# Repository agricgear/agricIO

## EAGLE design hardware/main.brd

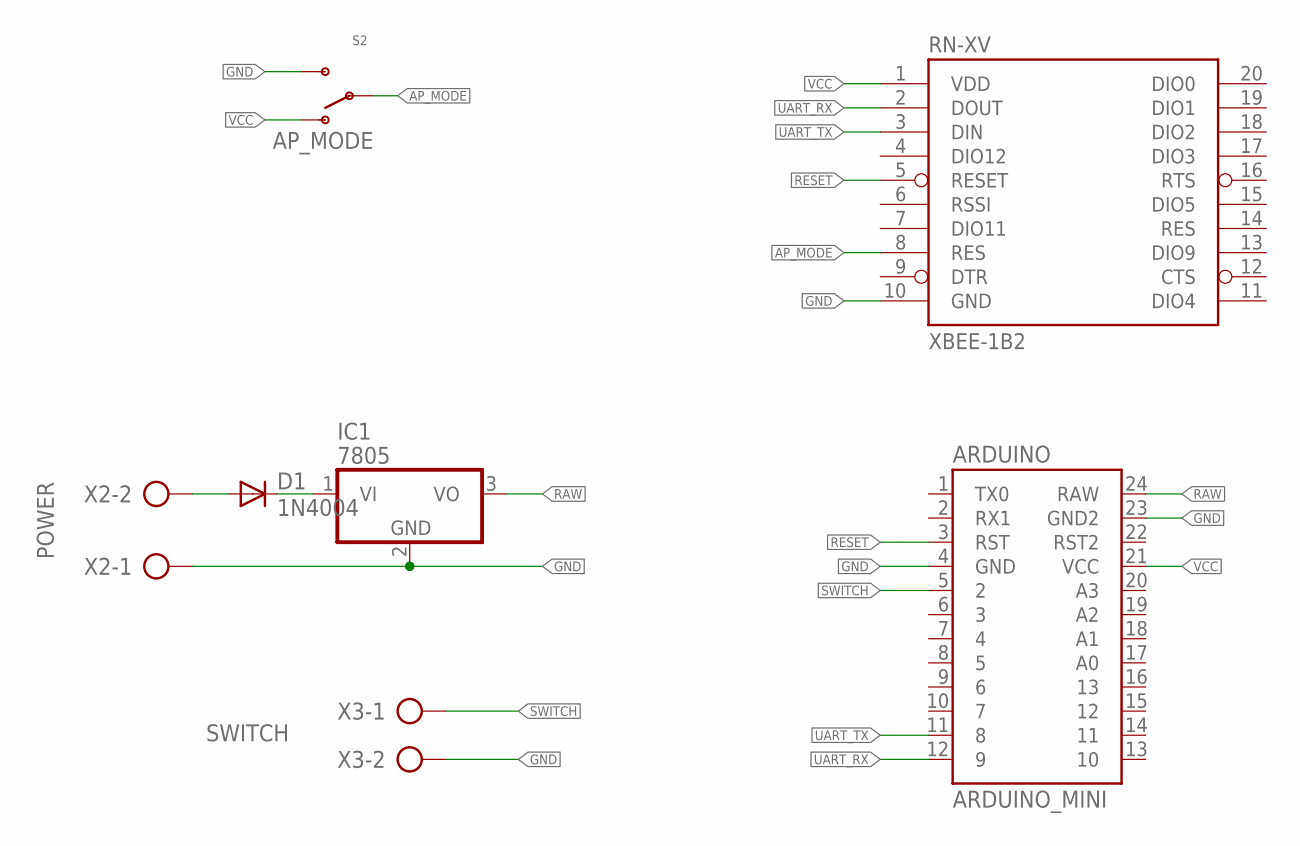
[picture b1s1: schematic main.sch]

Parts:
ARDUINO: ARDUINO_MINI
D1: 1N4004; DO41-10
IC1: 7805; TO220V
RN-XV: XBEE-1B2; XBEE-SILK
S2: AP_MODE; SWITCH-SPDT
X2: POWER; AK500/2
X3: SWITCH; AK500/2

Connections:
AP_MODE: RN-XV.8 (RES), S2.2
GND: ARDUINO.4 (GND), ARDUINO.23 (GND2), IC1.2 (GND), RN-XV.10 (GND), S2.3 (S), X2.1, X3.2
unnamed: D1.A, X2.2
unnamed: D1.C, IC1.1 (VI)
RAW: ARDUINO.24 (RAW), IC1.3 (VO)
RESET: ARDUINO.3 (RST), RN-XV.5 (RESET)
SWITCH: ARDUINO.5 (2), X3.1
UART_RX: ARDUINO.12 (9), RN-XV.2 (DOUT)
UART_TX: ARDUINO.11 (8), RN-XV.3 (DIN)
VCC: ARDUINO.21 (VCC), RN-XV.1 (VDD), S2.1 (O)

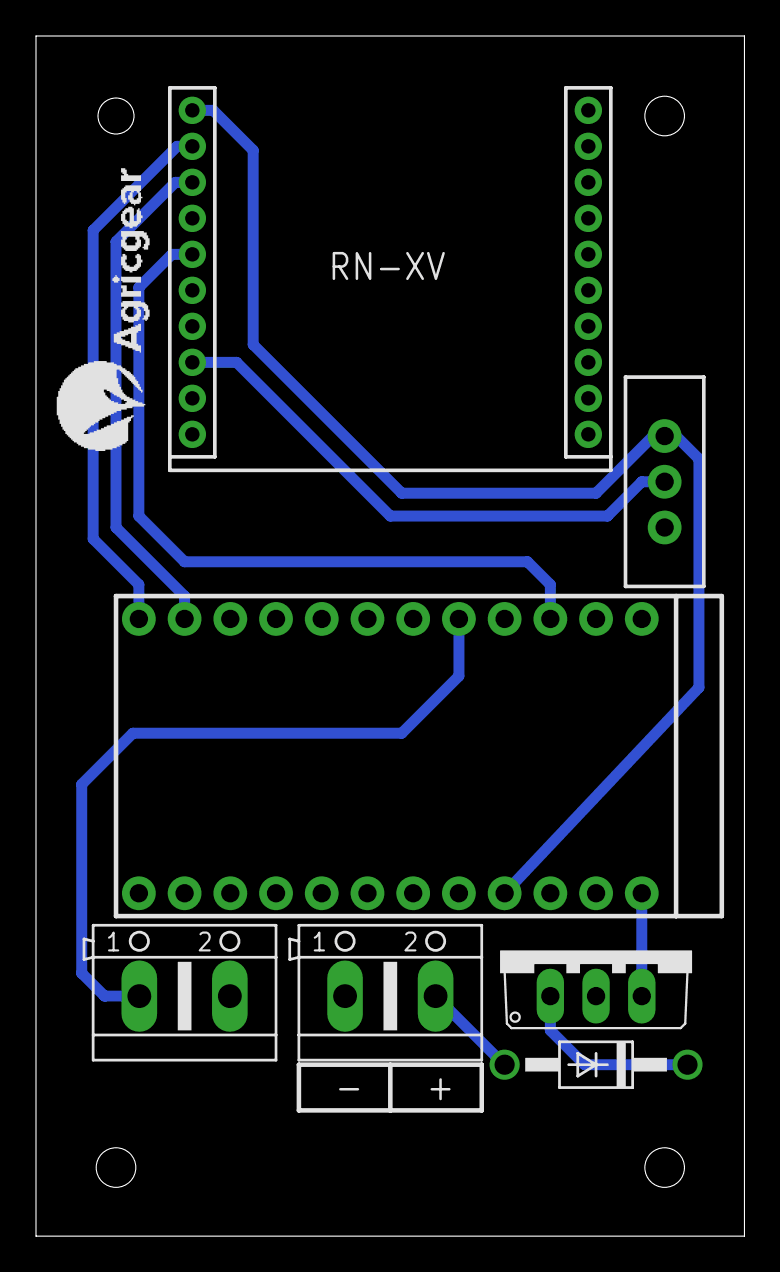
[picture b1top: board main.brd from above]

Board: 2 copper layers, 39.4 x 66.7 mm, 8 parts (0 on the bottom side), 10 nets.

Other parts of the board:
U$4: LOGO_AGROGUIA_SILK

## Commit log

2013-06-05 specs draft
2013-06-12 Added hardware files in EagleCad format
2013-06-12 Added firmware as Arduino sketch
2013-06-12 Added documentation files
2013-06-12 Removed specs.txt file
2013-06-12 Fixed some grammar and spelling
2013-06-12 Datasheets of Wifi module added
2013-06-12 Removed eagle.epf file
2013-06-12 Added A4 frame to schema
2013-06-12 Added PDF preview of schema and board
2013-07-08 Añadidos cambios sobre el hardware y el firmware del prototipo final.
2013-07-08 Añadido fichero backup de texto con los valores configurados en el modulo Wifly RN-XV
2013-11-02 - Añadido PSD usado para crear PCB en casa - Actualizado main.brd a version de eagle 6.5.0

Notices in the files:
parts and their libraries:
SparkFun-Electromechanical: Licensing: CC v3.0 Share-Alike You are welcome to use this library for commercial purposes.
